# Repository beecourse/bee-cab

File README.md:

bee-cab
=======

This [bee](https://github.com/beecourse) provides a **ca**pacitive measuring **b**ridge.
It is intended for use with the capacitive force sensor [S15-45N from SingleTact](https://www.singletact.com/micro-force-sensor/standard-sensors/15mm-standard-sensor/15mm-45newton/), which can be connected to J5.

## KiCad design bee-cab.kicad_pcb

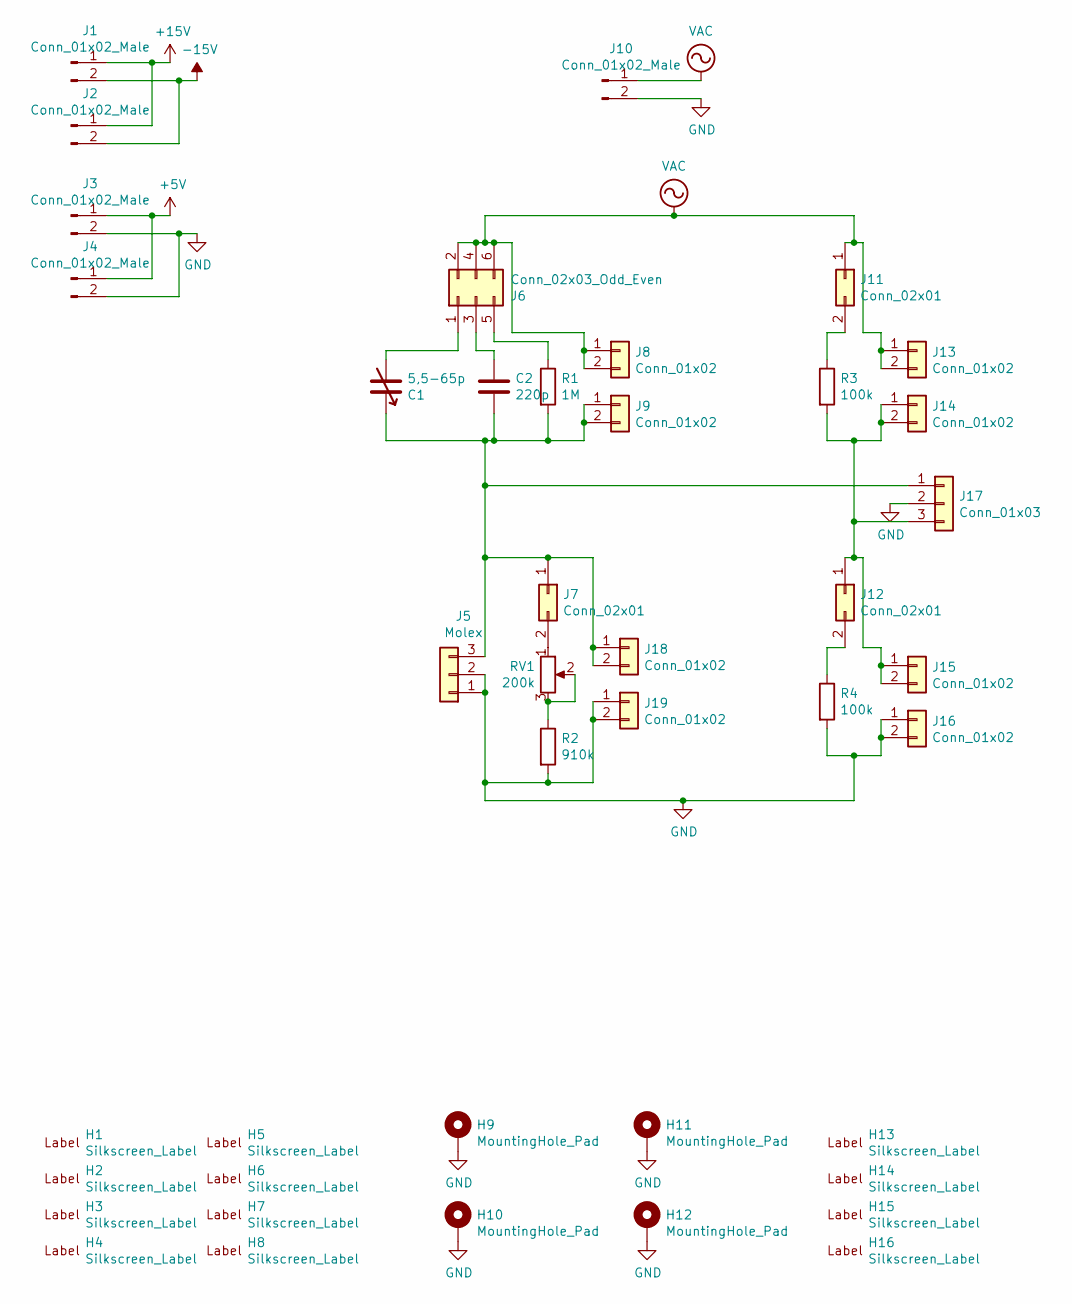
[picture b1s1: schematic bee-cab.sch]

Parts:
C1: 5,5-65p; C_Trimmer_Vishay_D10mm_Vertical_HolePattern5mmx10mm
C2: 220p; C_0805_2012Metric_Pad1.15x1.40mm_HandSolder
H1, H2: Silkscreen_Label; Text_U_B+_Silkscreen
H3, H4: Silkscreen_Label; Text_U_B-_Silkscreen
H5, H6: Silkscreen_Label; Text_U_B2_Silkscreen
H7, H8, H16: Silkscreen_Label; Symbol_GND_Silkscreen
H9, H10, H11, H12: MountingHole_Pad; MountingHole_3.2mm_M3_ISO7380_Pad
H13: Silkscreen_Label; EMT-Logo_5.1x2.5mm_Silkscreen
H14: Silkscreen_Label; BEE-Logo_Silkscreen_small
H15: Silkscreen_Label; Text_U_S_Silkscreen
J1, J2, J3, J4, J10: Conn_01x02_Male; PinHeader_1x02_P2.54mm_Vertical
J5: Molex; Molex_Easy-On_528070310_1x03_P1.0mm_Horizontal; Mouser Part No 538-52807-0310
J6: Conn_02x03_Odd_Even; PinHeader_2x03_P2.54mm_Vertical
J7, J11, J12: Conn_02x01; PinHeader_2x01_P2.54mm_Vertical
J8, J9, J13, J14, J15, J16, J18, J19: Conn_01x02; PinSocket_2x01_P2.54mm_Vertical
J17: Conn_01x03; PinHeader_1x03_P2.54mm_Vertical
R1: 1M; R_0805_2012Metric_Pad1.15x1.40mm_HandSolder
R2: 910k; R_0805_2012Metric_Pad1.15x1.40mm_HandSolder
R3, R4: 100k; R_0805_2012Metric_Pad1.15x1.40mm_HandSolder
RV1: 200k; Potentiometer_Bourns_3296W_Vertical

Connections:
+5V: J3.1, J4.1
+15V: J1.1, J2.1
-15V: J1.2, J2.2
GND: H9.1, H10.1, H11.1, H12.1, J3.2, J4.2, J5.1, J5.2, J10.2, J16.1, J16.2, J17.2, J19.1, J19.2, R2.2, R4.2
unnamed: C1.1, C2.2, J5.3, J7.1, J9.1, J9.2, J17.1, J18.1, J18.2, R1.2
unnamed: C1.2, J6.1
unnamed: C2.1, J6.3
unnamed: J6.5, R1.1
unnamed: J7.2, RV1.1
unnamed: J11.2, R3.1
unnamed: J12.1, J14.1, J14.2, J15.1, J15.2, J17.3, R3.2
unnamed: J12.2, R4.1
unnamed: R2.1, RV1.2, RV1.3
VAC: J6.2, J6.4, J6.6, J8.1, J8.2, J10.1, J11.1, J13.1, J13.2

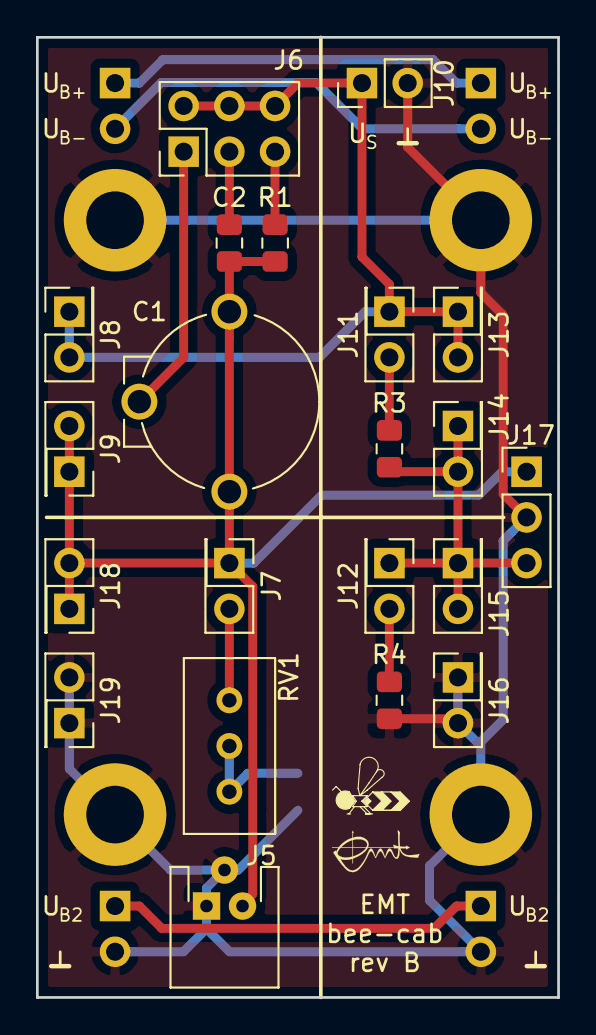
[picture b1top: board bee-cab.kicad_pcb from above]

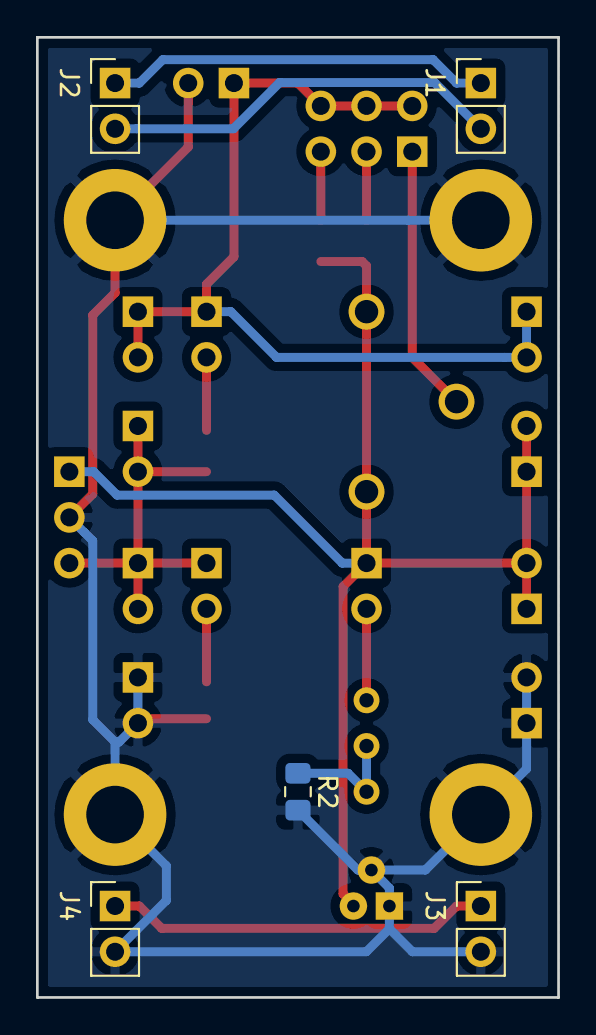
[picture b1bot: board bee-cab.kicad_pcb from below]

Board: 2 copper layers, 29.0 x 53.3 mm, 42 parts (5 on the bottom side), 14 nets.

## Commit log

2019-04-15 Add gitignore.
2019-04-15 Initialize from bee template.
2019-04-24 begin schematic
2019-04-25 Update schematic.
2019-04-26 Remove unnecessary jumpers.
2019-04-26 Add pin sockets for custom parts.
2019-04-26 Mirror pinheader to optimize PCB placement.
2019-04-26 Place parts on PCB.
2019-04-26 Flip rotary capacitor connection.
2019-04-26 Update project file.
2019-04-26 Layout.
2019-04-26 Place part references on silkscreen.
2019-04-29 Add sch symbols for labels, update PCB accordingly.
2019-04-29 Gitignore cache.
2019-04-29 Replace vias by mounting holes.
2019-04-29 Add ground plane.
2019-04-29 Hide mounting hole reference on silkscreen.
2019-04-30 Increase line width of seperator.
2019-05-03 Add text and logos.
2019-05-07 Add part numbers.
2019-05-10 Add pinheader for AC supply.
2019-05-10 Add silkscreen labels.
2019-05-10 Increase revision label to B.
2019-05-24 Fix capacitor value.
2020-07-01 Relabel as bee specific.
2020-07-15 Add license.
2020-07-15 Add readme.
2023-03-17 Add figure showing top view of PCB
